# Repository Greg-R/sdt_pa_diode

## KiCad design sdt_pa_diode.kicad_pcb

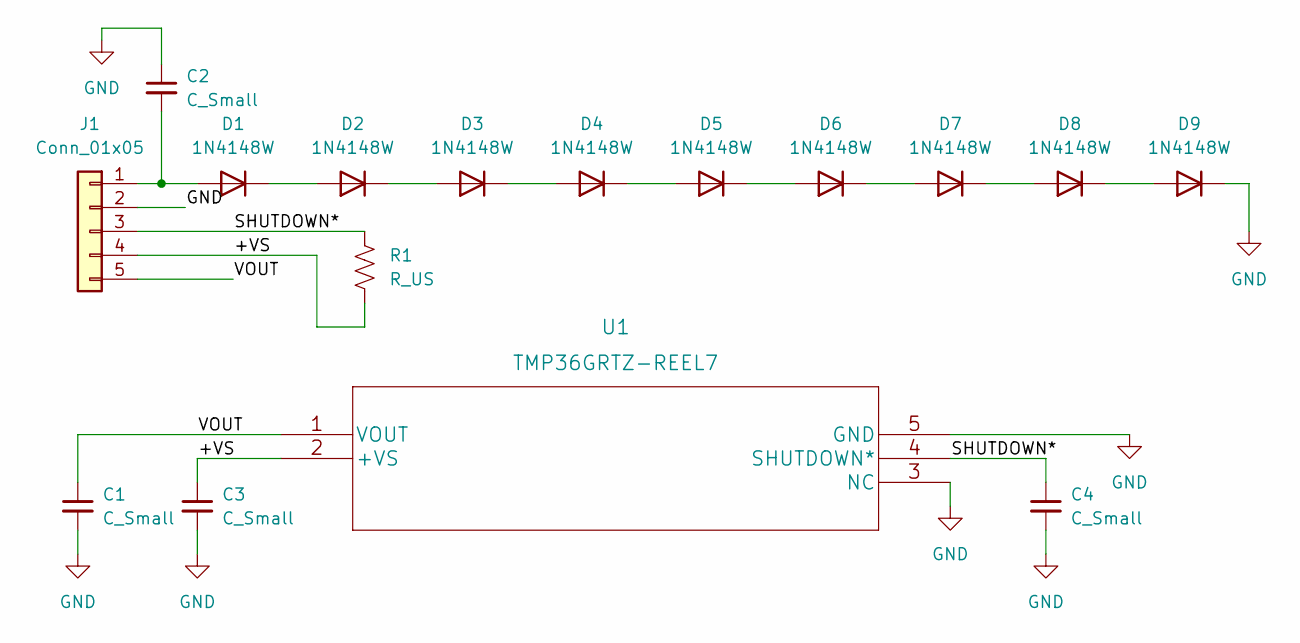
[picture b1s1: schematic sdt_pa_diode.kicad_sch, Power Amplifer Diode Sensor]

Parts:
C1, C2, C3, C4: C_Small; C_1206_3216Metric_Pad1.33x1.80mm_HandSolder
D1, D2, D3, D4, D5, D6, D7, D8, D9: 1N4148W; D_SOD-123
J1: Conn_01x05; PinHeader_1x05_P2.54mm_Horizontal
R1: R_US; R_1206_3216Metric_Pad1.30x1.75mm_HandSolder
U1: TMP36GRTZ-REEL7

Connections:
/+VS: C3.1, J1.4, R1.2, U1.2 (+VS)
/SHUTDOWN*: C4.1, J1.3, R1.1, U1.4 (SHUTDOWN*)
/VOUT: C1.1, J1.5, U1.1 (VOUT)
GND: C1.2, C2.1, C3.2, C4.2, D9.1 (K), J1.2, U1.3 (NC), U1.5 (GND)
unnamed: C2.2, D1.2 (A), J1.1
unnamed: D1.1 (K), D2.2 (A)
unnamed: D2.1 (K), D3.2 (A)
unnamed: D3.1 (K), D4.2 (A)
unnamed: D4.1 (K), D5.2 (A)
unnamed: D5.1 (K), D6.2 (A)
unnamed: D6.1 (K), D7.2 (A)
unnamed: D7.1 (K), D8.2 (A)
unnamed: D8.1 (K), D9.2 (A)

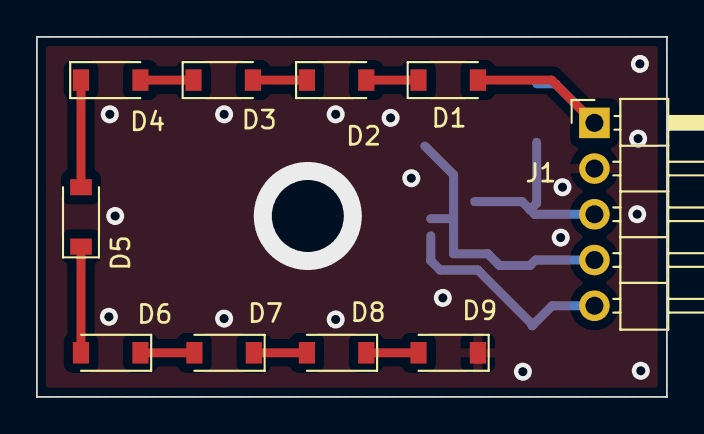
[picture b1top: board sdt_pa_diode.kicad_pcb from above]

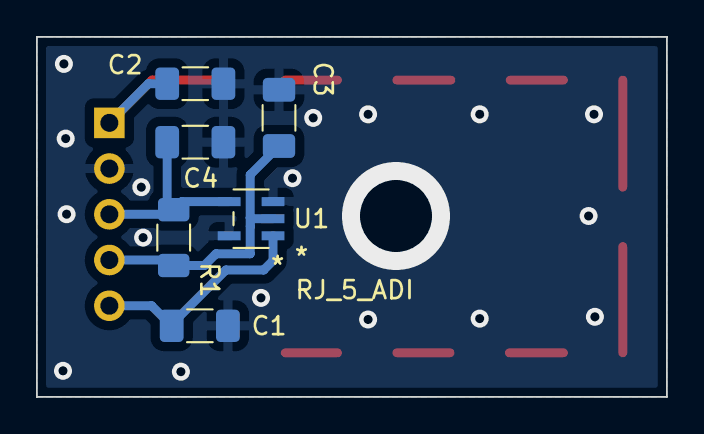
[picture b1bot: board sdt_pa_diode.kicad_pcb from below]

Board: 2 copper layers, 35.0 x 20.0 mm, 16 parts (6 on the bottom side), 13 nets.

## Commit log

2022-09-03 First layout started.
2022-09-09 Ready for first fab.

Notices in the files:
parts and their libraries:
Copyright 2021 Accelerated Designs. All rights reserved.
